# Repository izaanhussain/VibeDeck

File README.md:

# VibeDeck 

VibeDeck is my 9-key macropad, built for Hack Club's Hackpad / stardance challenge

I wanted to make something small and simple beacause i was new to these so that I could design and build myself, and decided to use a Seeed XIAO RP2040 as mentioned in (hackclubs docs )with 9 mechanical switches.

## What's in it

- 9 mechanical switches

- Seeed XIAO RP2040

- 1x SK6812MINI-E RGB LED

- USB-C

- Custom PCB (KiCad)

- Custom case (FreeCAD)

## Bill of Materials (BOM)

| Component | Quantity | Source |
|---|---:|---|
| Seeed Studio XIAO RP2040 | 1 | [Hack Club Hackpad Kit](https://blueprint.hackclub.com/hackpad/parts) |
| Cherry MX-compatible mechanical switches | 9 | [Hack Club Hackpad Kit](https://blueprint.hackclub.com/hackpad/parts) |
| SK6812 MINI-E RGB LED | 1 | [Hack Club Hackpad Kit](https://blueprint.hackclub.com/hackpad/parts) |

All three components are from the Hack Club hackpad kit.

## The PCB

Designed in KiCad; has 9 individual switch inputs and 1 SK6812MINI RGB LED input. KiCad's DRC is pretty strict, but I managed to fix all the errors and got a good result

## The Case

I used the [Custom Micropad](https://github.com/BenGreenberg07/custom-micropad) case by Ben Greenberg as a base for my own design, modifying it to fit my VibeDeck PCB. I exported my modified top and bottom parts as STEP files.

## Production 
 The production files are in the "production" folder where you can find the gerbers.zip

## Firmware (KMK / CircuitPython)

VibeDeck uses KMK firmware with CircuitPython, located in the `Firmware` directory. The 9 keys are directly connected to individual GPIOs on the XIAO RP2040, and the SK6812MINI is connected separately.

## File Structure

```text
VibeDeck/
├── CAD/
│   ├── VibeDeck_Bottom.step
│   └── VibeDeck_Top.step
├── Firmware/
│   └── main.py
├── PCB/
│   ├── VibeDeck.kicad_pcb
│   └── Vibedeck_schematic.kicad_sch
├── production/
│   └── gerbers.zip
├── bom.csv
└── README.md
```

## What I learned

This was my first ever PCB, so I learned a lot on the way. KiCad's PCB routing and DRC tools were a bit difficult to get use at first but however i learned how to make a complete working design! I also learned how to use FreeCAD and how the case parts interact with the PCB. The projecy=t is fully completed and the given code works.

The case design was also quite challenging, and required many iterations before I was satisfied with the result.

## Credits
everything is made by me just the case as mentioned in the case section. i DONt know how to write a readme and this is not AI. Thanks to stardance for sponsoring this project and many more 

| Hack Club's Hackpad / Stardance challenge | [Hack Club](https://hackclub.com/) |

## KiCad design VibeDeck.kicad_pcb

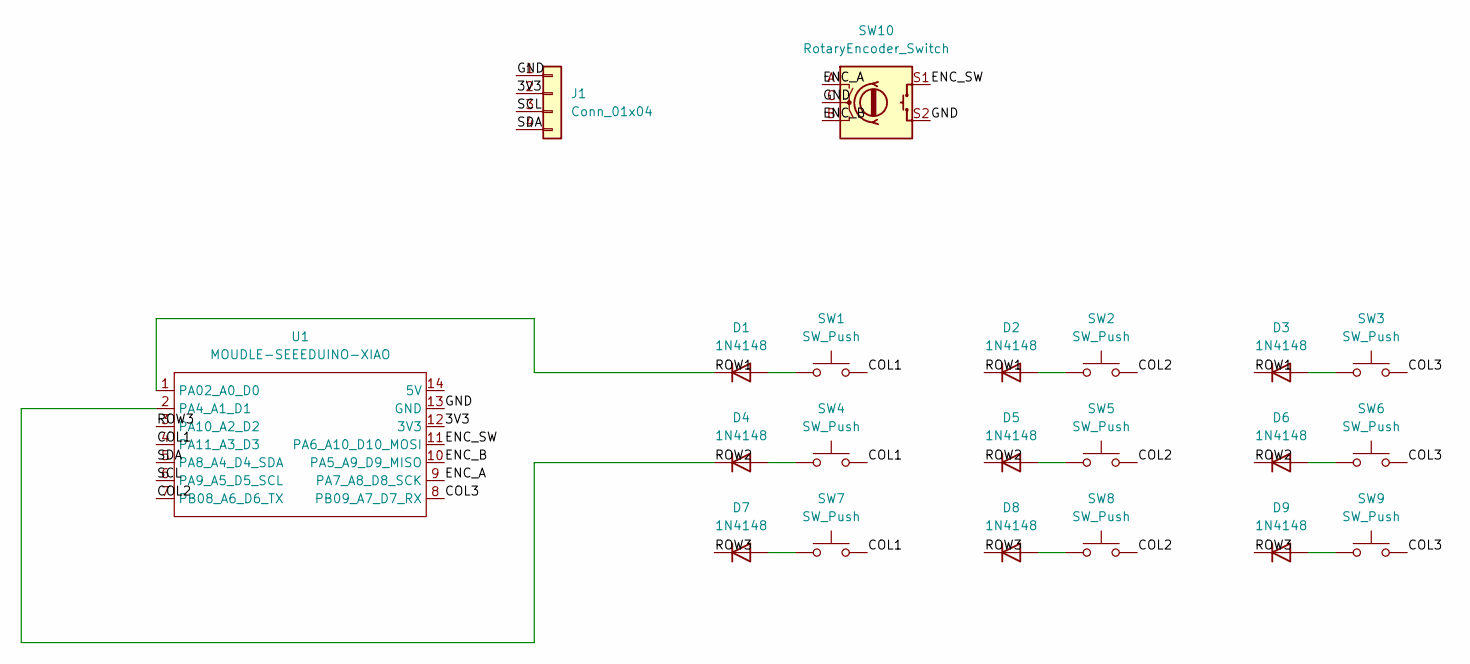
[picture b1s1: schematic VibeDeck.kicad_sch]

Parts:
D1, D2, D3, D4, D5, D6, D7, D8, D9: 1N4148; D_DO-35_SOD27_P7.62mm_Horizontal
J1: Conn_01x04; FanPinHeader_1x04_P2.54mm_Vertical
SW1, SW2, SW3, SW4, SW5, SW6, SW7, SW8, SW9: SW_Push; SW_Cherry_MX_1.00u_PCB
SW10: RotaryEncoder_Switch; RotaryEncoder_Alps_EC11E-Switch_Vertical_H20mm
U1: MOUDLE-SEEEDUINO-XIAO; XIAO-Generic-Hybrid-14P-2.54-21X17.8MM

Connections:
/3V3: J1.2, U1.12 (3V3)
/COL1: SW1.2, SW4.2, SW7.2, U1.4 (PA11_A3_D3)
/COL2: SW2.2, SW5.2, SW8.2, U1.7 (PB08_A6_D6_TX)
/COL3: SW3.2, SW6.2, SW9.2, U1.8 (PB09_A7_D7_RX)
/ENC_A: SW10.A, U1.9 (PA7_A8_D8_SCK)
/ENC_B: SW10.B, U1.10 (PA5_A9_D9_MISO)
/ENC_SW: SW10.S1, U1.11 (PA6_A10_D10_MOSI)
/GND: J1.1, SW10.C, SW10.S2, U1.13 (GND)
/ROW1: D1.1 (K), D2.1 (K), D3.1 (K), U1.1 (PA02_A0_D0)
/ROW2: D4.1 (K), D5.1 (K), D6.1 (K), U1.2 (PA4_A1_D1)
/ROW3: D7.1 (K), D8.1 (K), D9.1 (K), U1.3 (PA10_A2_D2)
/SCL: J1.3, U1.6 (PA9_A5_D5_SCL)
/SDA: J1.4, U1.5 (PA8_A4_D4_SDA)
unnamed: D1.2 (A), SW1.1
unnamed: D2.2 (A), SW2.1
unnamed: D3.2 (A), SW3.1
unnamed: D4.2 (A), SW4.1
unnamed: D5.2 (A), SW5.1
unnamed: D6.2 (A), SW6.1
unnamed: D7.2 (A), SW7.1
unnamed: D8.2 (A), SW8.1
unnamed: D9.2 (A), SW9.1

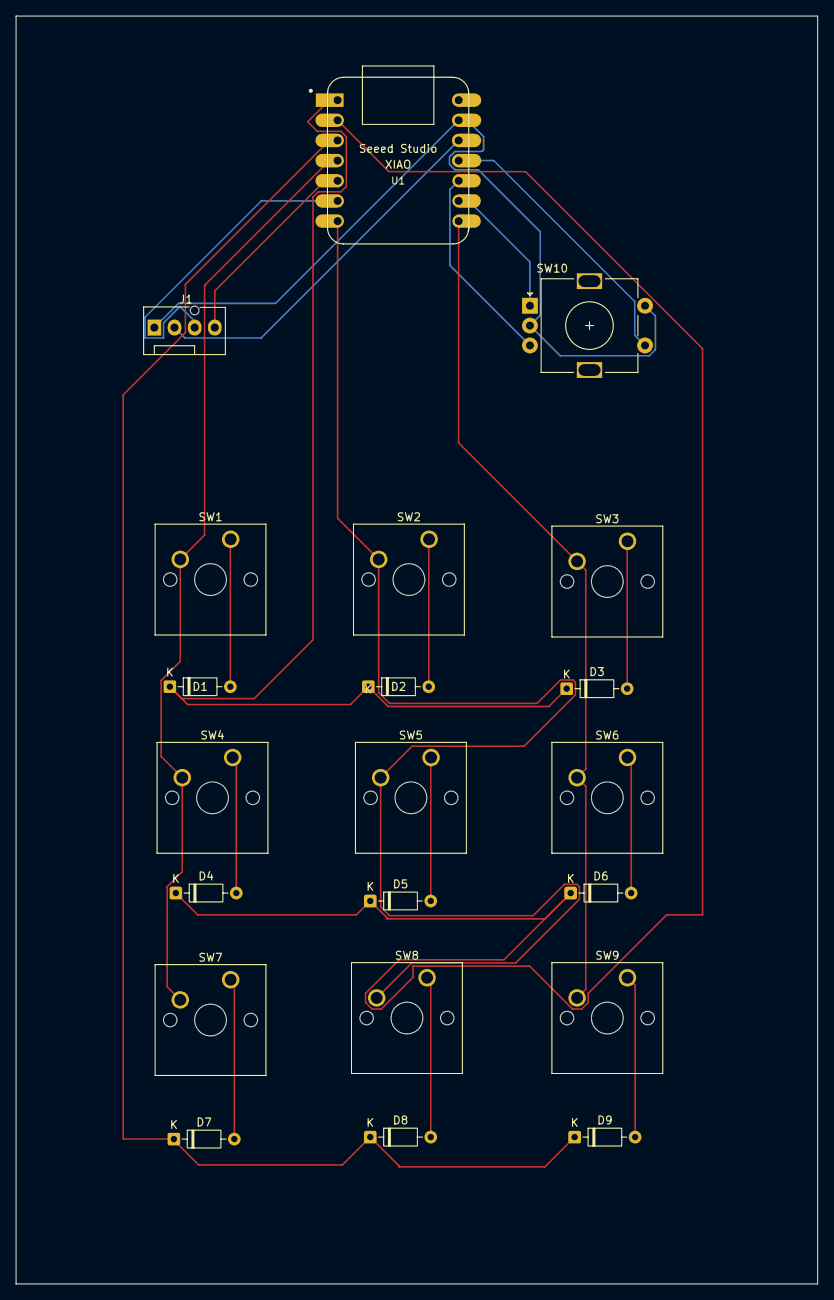
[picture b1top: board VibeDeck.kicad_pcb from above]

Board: 2 copper layers, 101.0 x 159.8 mm, 21 parts (0 on the bottom side), 22 nets.

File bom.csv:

Designator,Footprint,Quantity,Value,LCSC Part #
D1,LED_SK6812MINI_PLCC4_3.5x3.5mm_P1.75mm,1,SK6812MINI,https://blueprint.hackclub.com/hackpad/parts
"SW1, SW2, SW3, SW4, SW5, SW6, SW7, SW8, SW9",SW_Cherry_MX_1.00u_PCB,9,SW_Push,https://blueprint.hackclub.com/hackpad/parts
U1,XIAO-RP2040-DIP,1,XIAO-RP2040-DIP,https://wiki.seeedstudio.com/XIAO-RP2040/

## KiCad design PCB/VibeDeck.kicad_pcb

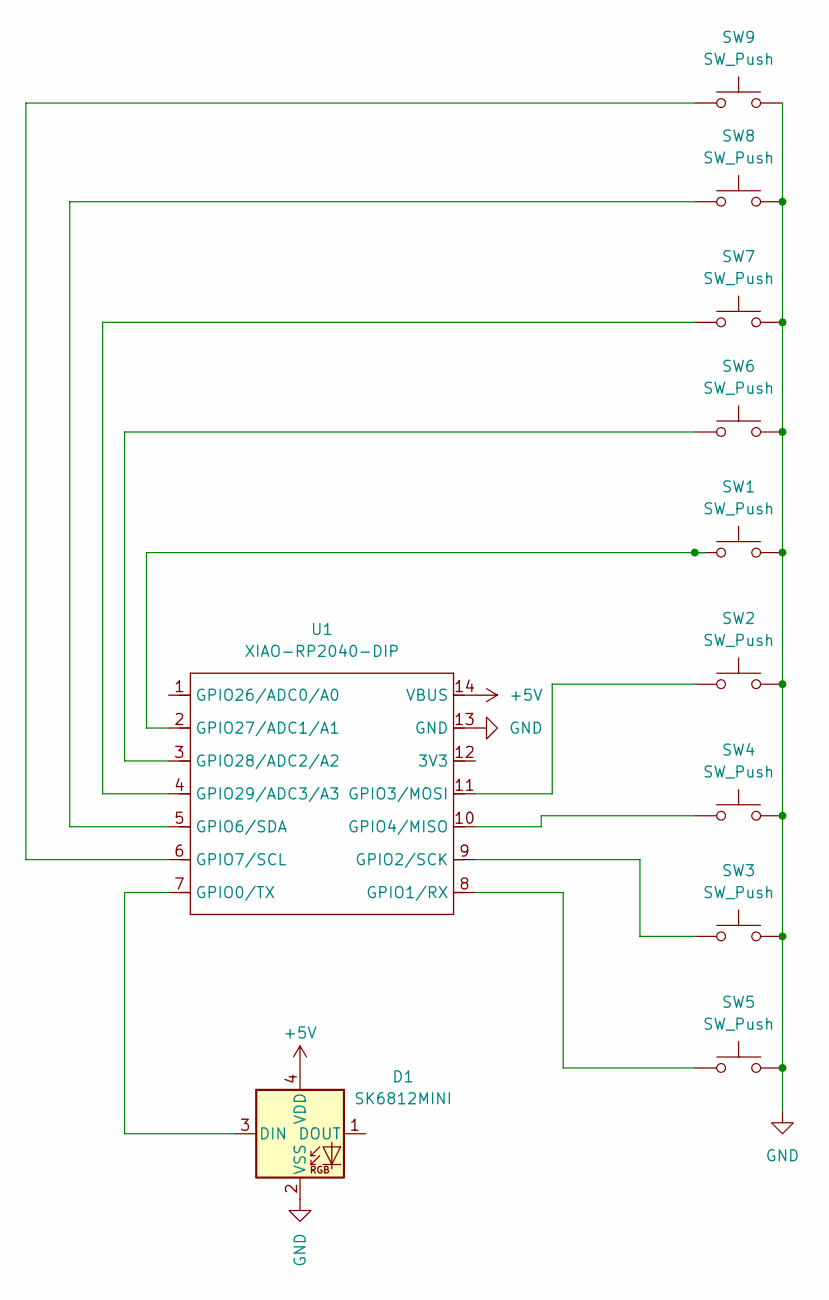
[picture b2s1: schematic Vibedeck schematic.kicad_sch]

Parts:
D1: SK6812MINI; LED_SK6812MINI_PLCC4_3.5x3.5mm_P1.75mm
SW1, SW2, SW3, SW4, SW5, SW6, SW7, SW8, SW9: SW_Push; SW_Cherry_MX_1.00u_PCB
U1: XIAO-RP2040-DIP

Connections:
+5V: D1.4 (VDD), U1.14 (VBUS)
GND: D1.2 (VSS), SW1.2, SW2.2, SW3.2, SW4.2, SW5.2, SW6.2, SW7.2, SW8.2, SW9.2, U1.13 (GND)
unnamed: D1.3 (DIN), U1.7 (GPIO0/TX)
unnamed: SW5.1, U1.8 (GPIO1/RX)
unnamed: SW3.1, U1.9 (GPIO2/SCK)
unnamed: SW2.1, U1.11 (GPIO3/MOSI)
unnamed: SW4.1, U1.10 (GPIO4/MISO)
unnamed: SW8.1, U1.5 (GPIO6/SDA)
unnamed: SW9.1, U1.6 (GPIO7/SCL)
unnamed: SW1.1, U1.2 (GPIO27/ADC1/A1)
unnamed: SW6.1, U1.3 (GPIO28/ADC2/A2)
unnamed: SW7.1, U1.4 (GPIO29/ADC3/A3)

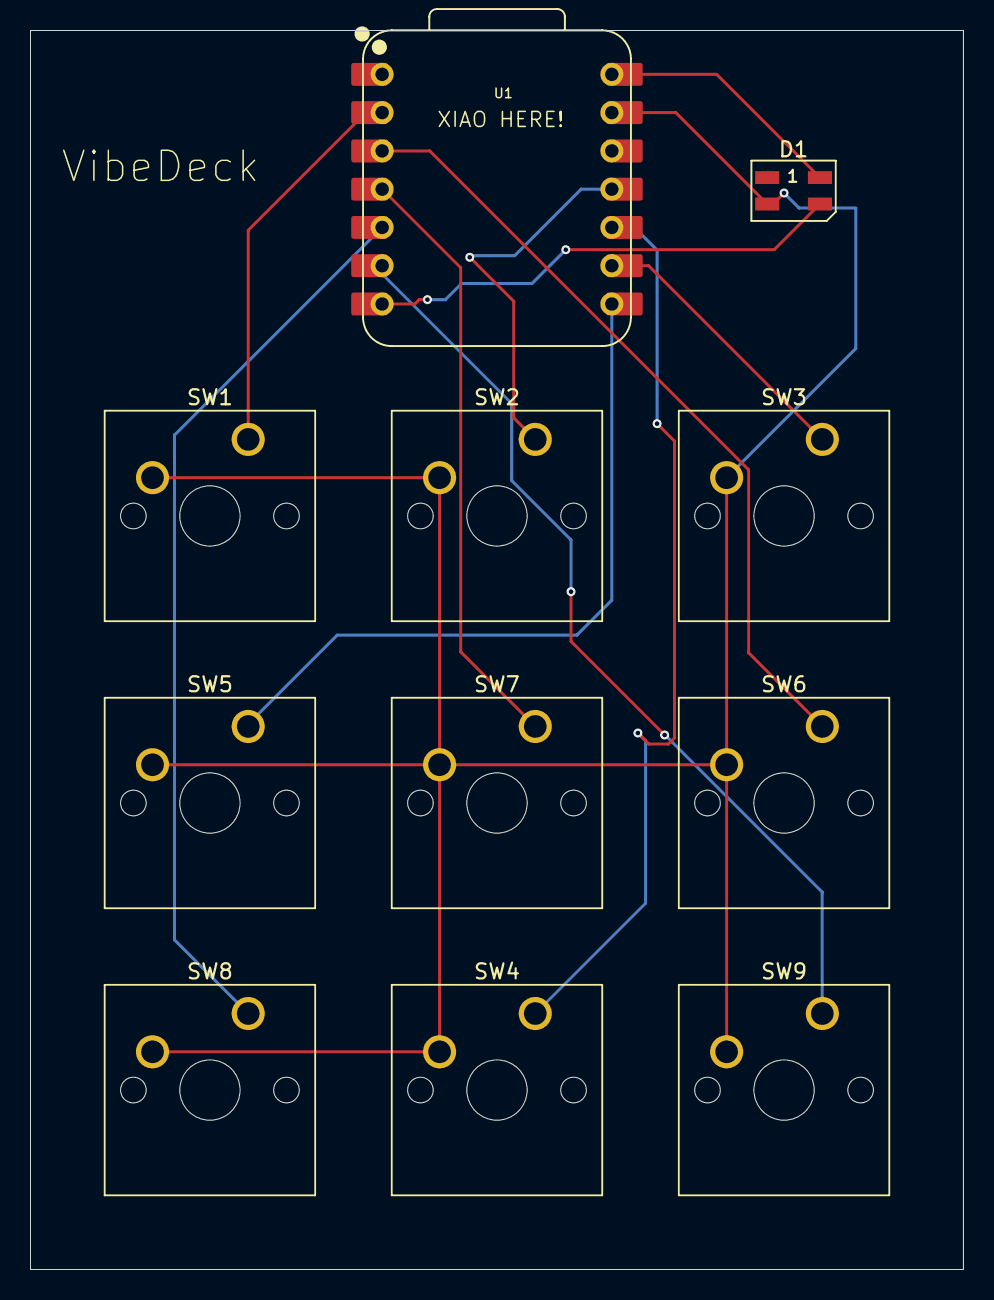
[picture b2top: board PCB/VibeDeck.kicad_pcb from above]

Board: 2 copper layers, 61.9 x 82.2 mm, 11 parts (0 on the bottom side), 12 nets.

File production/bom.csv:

Designator,Footprint,Quantity,Value,LCSC Part #
D1,LED_SK6812MINI_PLCC4_3.5x3.5mm_P1.75mm,1,SK6812MINI,
"SW1, SW2, SW3, SW4, SW5, SW6, SW7, SW8, SW9",SW_Cherry_MX_1.00u_PCB,9,SW_Push,
U1,XIAO-RP2040-DIP,1,XIAO-RP2040-DIP,
